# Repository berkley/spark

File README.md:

spark
=====
Spark.io and Node.js controlled home automation (currently: LED lighting and watering system)

Overview
========
Integrated home automation controls.  This app and firmware currently have two modules: 1) LED pixel controls 2) Solenoid based sprinkler system controls

* Control neopixel LED strips connected to one or more Spark Core (http://spark.io) processors with a web interface.  You can use this to control various parts of your house lighting, an art project or whatever else you want to program.  Use the /lights route on the node app to control lighting.  

* Control your watering system.  Configure pins D0-D7 to control solenoid valves via transistors or relays.  

You'll need to flash each of your cores with the appropriate firmware, then run the node.js server on a computer with access to the internet.  

See the README in each subdirectory for a more detailed description of its contents.

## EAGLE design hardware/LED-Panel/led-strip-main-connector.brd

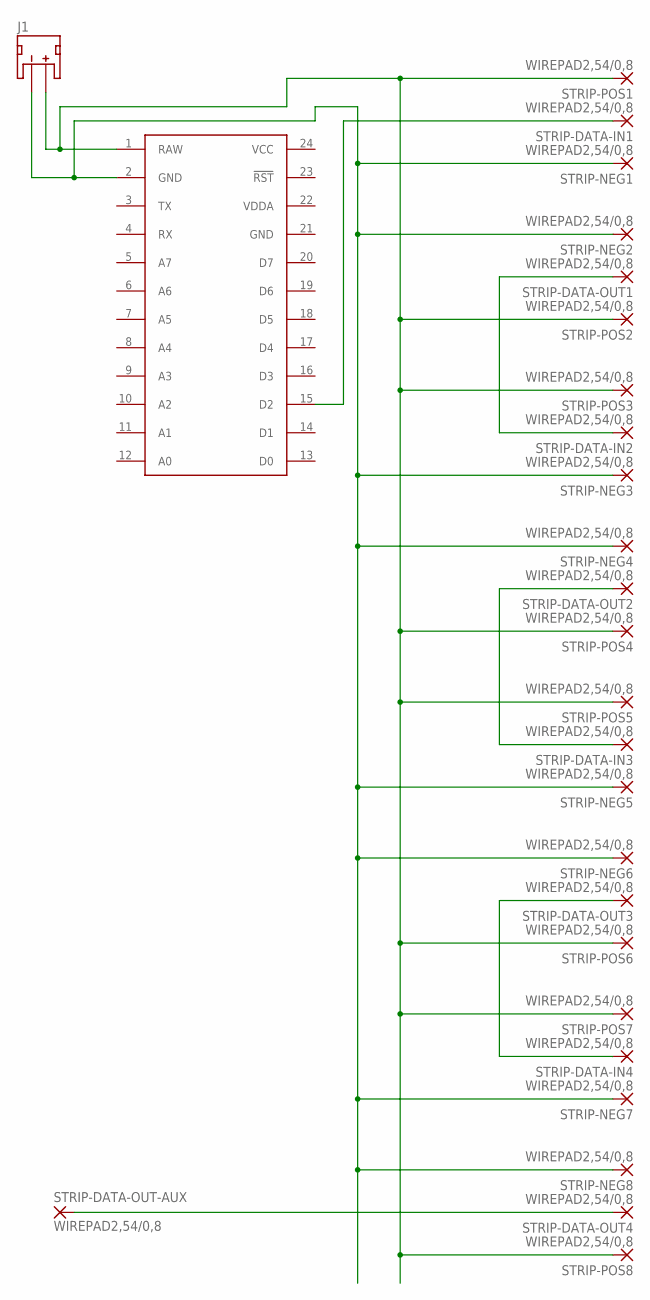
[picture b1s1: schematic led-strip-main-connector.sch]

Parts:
J1: 1; JST-2-SMD
SPARK_CORE: SPARK_CORECORE; SPARK_CORE
STRIP-DATA-IN1, STRIP-DATA-IN2, STRIP-DATA-IN3, STRIP-DATA-IN4: WIREPAD2,54/0,8; 2,54/0,8
STRIP-DATA-OUT1, STRIP-DATA-OUT2, STRIP-DATA-OUT3, STRIP-DATA-OUT4: WIREPAD2,54/0,8; 2,54/0,8
STRIP-DATA-OUT-AUX: WIREPAD2,54/0,8; 2,54/0,8
STRIP-NEG1, STRIP-NEG2, STRIP-NEG3, STRIP-NEG4, STRIP-NEG5, STRIP-NEG6, STRIP-NEG7, STRIP-NEG8: WIREPAD2,54/0,8; 2,54/0,8
STRIP-POS1, STRIP-POS2, STRIP-POS3, STRIP-POS4, STRIP-POS5, STRIP-POS6, STRIP-POS7, STRIP-POS8: WIREPAD2,54/0,8; 2,54/0,8

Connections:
GND: SPARK_CORE.21 (GND)
unnamed: SPARK_CORE.15 (D2), STRIP-DATA-IN1.1
unnamed: STRIP-DATA-IN2.1, STRIP-DATA-OUT1.1
unnamed: J1.1 (-), SPARK_CORE.2 (GND), STRIP-NEG1.1, STRIP-NEG2.1, STRIP-NEG3.1, STRIP-NEG4.1, STRIP-NEG5.1, STRIP-NEG6.1, STRIP-NEG7.1, STRIP-NEG8.1
unnamed: J1.2 (+), SPARK_CORE.1 (RAW), STRIP-POS1.1, STRIP-POS2.1, STRIP-POS3.1, STRIP-POS4.1, STRIP-POS5.1, STRIP-POS6.1, STRIP-POS7.1, STRIP-POS8.1
unnamed: STRIP-DATA-IN3.1, STRIP-DATA-OUT2.1
unnamed: STRIP-DATA-IN4.1, STRIP-DATA-OUT3.1
unnamed: STRIP-DATA-OUT4.1, STRIP-DATA-OUT-AUX.1
VCC: SPARK_CORE.24 (VCC)
VDDA: SPARK_CORE.22 (VDDA)

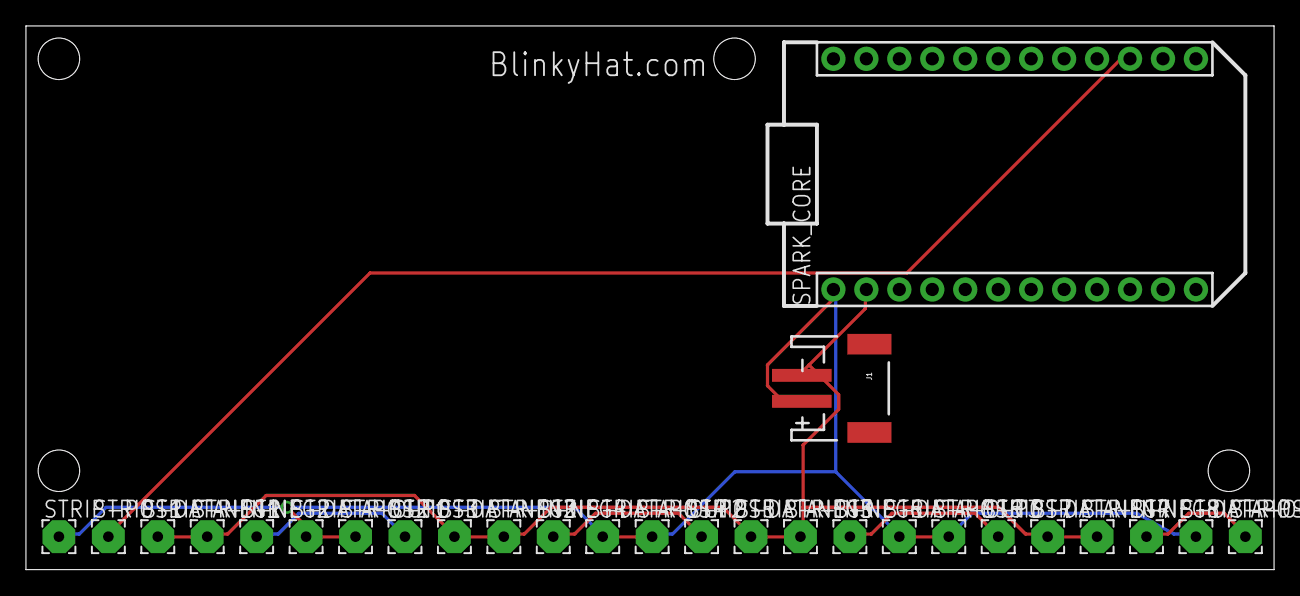
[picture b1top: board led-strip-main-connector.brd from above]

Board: 2 copper layers, 96.2 x 41.9 mm, 27 parts (0 on the bottom side), 7 nets.

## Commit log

2014-11-04 moving files from berkley/arduino
2014-11-04 readme
2014-11-04 adding readme
2014-11-04 updating docs and refactoring
2014-11-04 adding stuff for spark
2014-11-05 more fixes
2014-11-05 updating syntax
2014-11-05 Update README.md
    updated syntax
2014-11-05 changing to templated system
2014-11-05 moving access_token and url to config
2014-11-05 updating
2014-11-05 updating readme
2014-11-05 more readmes
2014-11-05 renaming ino file
2014-11-05 adding 'all' to the cores menu
2014-11-05 adding all
2014-11-05 Added led-strip-particles lib
2014-11-05 particle tweaks
2014-11-06 Updating readme.
2014-11-13 put MAX_COLORS back to 255
2014-11-13 Added config.example.json, removed config.json and added it to .gitignore
2014-11-14 adding async for multi-core posts
2014-11-14 end run animation
2014-11-14 Copied spark.js from master.
2014-11-15 adding particles to the webapp
2014-11-19 Fixed "sticky pixel" bug by changing tailLength var to double from uint8_t.
2014-11-19 updated ino with new particle code fixes
2014-11-19 adding more web params for particles
2014-11-19 the webapp now queries the core to set the values on the webapp to the current settings of the core
2014-11-19 state check happens when coreId changes now
2014-12-03 changes for dual pulse code...not yet working
2014-12-03 adding pixel counts for the two cores I have
2014-12-03 playing with adding color sliders dynamically
2014-12-03 add js to dynamically add colors
2014-12-06 added websocket response on the core, basic node app to connect and send pixel values
2014-12-09 multi-socket comms
2014-12-10 made new address space across multiple cores
2014-12-10 added sample config
2014-12-16 lots of WS stuff
2014-12-16 adding sparkle
2014-12-16 added web interface
2014-12-20 adding new block size and snow white balance
2014-12-28 fixing a couple bugs
2015-02-05 added wiring config
2015-03-03 lots of fixed and changes. setVBMP mostly works now
2015-03-03 add a flag to reset array to 0,0,0 before writing the bmp so that the command to reset the screen does not slow down the websocket processing
2015-03-04 added ability to write bmps to memory, then manipulate them over ws
2015-03-08 changes to websocket i'm not ready to merge yet
2015-03-10 messages sent in json. refactor sockets/screens with test harness and util
2015-03-10 more async fun
2015-03-11 adding websocket transaction test harness
2015-03-11 lots of good changes
2015-03-13 more websocket testing and debugging
2015-03-13 more testing
2015-03-16 testing for sockets
2015-03-17 working on getting ws to work with raspberry pi
2015-03-17 fixing serial number
2015-03-18 more socket tests
2015-03-20 socket comms to multiple cores working
2015-03-20 moving directory
2015-03-20 cleaning up
2015-03-20 reorganizing
2015-03-20 reorg
2015-03-20 cleanup
2015-03-20 added sendDelay
2015-03-21 multiple hats working on raspi wifi
2015-03-24 new animations
2015-03-24 adding more base functions to screen
2015-03-24 updating config example
2015-03-25 adding some simple content scripts
2015-03-25 multi-screen rendering
2015-03-25 added wraparound and no-wraparound modes
2015-03-27 added all-off script
2015-03-27 new animation stuff
2015-03-27 adding test scripts
2015-03-27 x-screen, no-wrap and wrap all work now
2015-03-27 added define for debug
2015-03-29 adding primitive functions and a test for them
2015-03-30 added test for setPixel
2015-03-31 adding code to display more than one bmp at a time
2015-04-01 adding eagle hardware designs
2015-04-10 updating eagle files
2015-04-22 adding fog script and fixing memory allocation for 32x8 bitmaps
2015-05-09 adding flash capabilities
2015-05-16 adding brightness params
2015-05-18 adding brightness controls and some ugly borders
2015-05-19 adding weather underground api call
2015-05-19 adding weather parsing
2015-05-24 refactoring to allow this app to have more than just lighting routes
2015-05-24 more refactoring for extening control to non-lights
2015-05-26 adding routes and views for water controls
2015-05-26 refactoring for water valve selection
2015-05-26 corename/id lookup works
2015-05-26 adding water controller firmware and node code to talk to it
2015-05-26 refactor pin control code
2015-05-26 making sure all pins are off on init
2015-05-26 updating readme and config example
2015-05-26 adding image
2015-05-26 added schematic
2015-05-26 adding image size.
2015-05-26 removed old comments.
2015-06-05 adding security sketch
2015-06-05 adding files
2015-06-05 added 6 pin monitoring
2015-06-05 renaming
2015-06-05 reversing changes to websocket code
2015-06-27 added USA program
2015-06-28 adding ino file for the water and security controller
2015-06-29 adding water-security controller
2015-06-29 adding door monitor
2015-07-17 adding cores to water valves
2015-07-22 adding linkback
2015-08-14 photon changes for websockets
2015-08-14 new controller for freddy eyes
2015-08-17 adding freddy sketch
2015-08-17 adding socket comms
2015-08-18 socket comms working
2015-08-18 working sockets
2015-08-18 added sequences and web interface
2015-08-23 adding fire routines
2015-08-24 adding local compile script and libs
2015-08-25 lots of stuff
2015-08-25 adding camp fire controller
2015-08-25 adding jquery
2015-08-26 adding beacon code
2015-08-28 adding keitheyes
2015-09-22 adding beer sensor sketch
2015-09-22 adding todo notes
2015-09-23 refactor and adding persistent storage
2015-09-26 added functions to animate when beer is flowing and to change the handle color gradually as the keg is depleted.
2015-09-26 removing setpixel call
2015-09-28 fixed compile error
2015-10-06 new host
2015-10-06 working beer app
2015-10-09 updating code
2015-10-09 fixing particle lib
2015-10-12 skull file
2015-10-12 adding lightning strobe
2015-10-12 added lightning to the node app
2015-10-14 adding the strip to the skull program and adding it to the node app
2015-10-14 adding non-lightning version of the skull app
2015-10-14 fixing mistaken commit on index.ejs
2015-10-14 added flag so that controllers that are not light controllers cna be removed from the GUI.
2015-10-14 fixing example config
2015-10-16 changed port order
2015-10-23 adding multi-tap support
2015-10-23 mostly got 3 tap working
2015-10-26 multi tap success
2015-10-27 adding sketch for suspenders
2015-10-27 trying tcp sockets for comms
2015-10-27 trying to add audio
2015-10-28 got audio metering working with the color wheel
2015-10-28 reverting freddy file
2015-10-28 reverting freddy changes
2015-10-29 soundhat working
2015-11-05 refactor to use structs to store tap info
2015-11-05 added EEPROM writing
2015-11-05 added published events
2015-11-05 refactor
2015-11-06 node app to push beer stats to insights
2015-11-06 added package.json
2015-11-06 cleaned up firmware, made it emit only 2 events, start and stop flow with total usage on the stop event
2015-11-06 sending int data now
2015-11-06 added docs on new variable to readme
2015-11-07 remove xmlization
2015-11-09 added docs on setPulseCount
2015-11-09 adding images
2015-11-09 adding photos.
2015-11-09 updating text.
2015-11-09 adding more description.
2015-11-10 trying to add gain to the suspenders
2015-11-11 beer stuff
2015-11-22 adding chicken controller code
2015-11-22 adding chicken controller
2015-11-22 adding chicken controller to homepage
2015-12-11 adding app to control fs beer
2015-12-11 adding style and ajax calls
2015-12-11 added better styling and ajax
2015-12-11 added beer emoji
2015-12-11 fixed bug in firmware, added percent to UI
2015-12-11 changed code to use config file
2015-12-11 adding nconf to package
2015-12-22 fixed bug where non-anmiation would not stop an animation
2015-12-22 adding dependencies and build file
2015-12-22 added ability to control strips and on/off devices
2015-12-23 firmware now remembers previous state of neopixel strip and A0-A5 pins
2015-12-23 add doc line
2015-12-23 refactoring and cleaning up
2015-12-23 persist brightness
2015-12-27 beginning of a rewrite for the UI
2016-01-02 working on ui changes for light controller
2016-01-03 more refactoring
2016-01-15 adding ui elements
2016-01-15 updated eeprom writing for beer firmware
2016-01-16 readding publish events
2016-08-29 bike lights
2016-08-29 adding bike code
2016-08-30 added 2 bike modes
2016-08-30 adding rotating bike program
2016-09-13 more bike stuff
2016-10-02 update pixel count
2016-10-23 working bike code with buttons
2016-10-24 horn button now connects to particle cloud
2016-10-31 soundhat
2016-10-31 skull stuff
2016-10-31 adding build file
2016-10-31 adding neopixel lib
2016-10-31 skull
2016-10-31 updating pixel count
2016-11-24 adding script to turn the chicken heat lamp on when the temp is 40 or less
2016-12-17 skull build files
2016-12-17 code and build for the neopixel light toy for the kids
2016-12-30 added system mode switch when you hold down the encoder button on startup
2017-01-11 updates for ellie
2017-01-26 adding code for 2 rotary encoders
2017-02-14 adding blinking selection cursor
2017-02-15 add displayArr to memory.
2017-02-15 added hold to clear func.
2017-03-03 adding yuba bike code to master
2017-03-14 update of url
2017-08-26 Added 'letters' program
2017-08-26 all letters configured and working
2017-08-26 Can adjust randomColor max brightness
2017-08-26 spell words in sequence
2017-08-27 Added initCGSign, cgSign_word and cgSign_letterSequence, and WORD_LENGTH macro.
2017-08-27 letter seq and words
2017-08-27 sign working
2017-08-27 mixed particles in with party sign
2017-08-27 particle duration * 4
2017-08-27 reduced particle count and added lic me
2017-09-16 added semi auto mode
2018-11-25 updating for new water controller
2018-11-25 adding crontab
2018-11-25 config backup
2019-04-05 added gorge water controller
2020-05-06 rainbow and particle mode
2020-05-06 Bump ejs from 0.8.8 to 3.1.2 in /node/beer-control
    Bumps [ejs](https://github.com/mde/ejs) from 0.8.8 to 3.1.2.
    - [Release notes](https://github.com/mde/ejs/releases)
    - [Changelog](https://github.com/mde/ejs/blob/master/CHANGELOG.md)
    - [Commits](https://github.com/mde/ejs/commits/v3.1.2)
2020-05-06 Bump ws from 0.6.5 to 7.2.5 in /node
    Bumps [ws](https://github.com/websockets/ws) from 0.6.5 to 7.2.5.
    - [Release notes](https://github.com/websockets/ws/releases)
    - [Commits](https://github.com/websockets/ws/compare/0.6.5...7.2.5)
2020-05-06 Bump debug from 2.0.0 to 4.1.1 in /node/beer-control
    Bumps [debug](https://github.com/visionmedia/debug) from 2.0.0 to 4.1.1.
    - [Release notes](https://github.com/visionmedia/debug/releases)
    - [Commits](https://github.com/visionmedia/debug/compare/2.0.0...4.1.1)
2020-05-06 Bump express from 3.4.4 to 4.17.1 in /node
    Bumps [express](https://github.com/expressjs/express) from 3.4.4 to 4.17.1.
    - [Release notes](https://github.com/expressjs/express/releases)
    - [Changelog](https://github.com/expressjs/express/blob/master/History.md)
    - [Commits](https://github.com/expressjs/express/compare/3.4.4...4.17.1)
2020-05-06 Bump morgan from 1.3.2 to 1.10.0 in /node/beer-control
    Bumps [morgan](https://github.com/expressjs/morgan) from 1.3.2 to 1.10.0.
    - [Release notes](https://github.com/expressjs/morgan/releases)
    - [Changelog](https://github.com/expressjs/morgan/blob/master/HISTORY.md)
    - [Commits](https://github.com/expressjs/morgan/compare/1.3.2...1.10.0)

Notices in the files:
parts and their libraries:
SparkFun-Connectors: Licensing: Creative Commons ShareAlike 4.0 International - https://creativecommons.org/licenses/by-sa/4.0
